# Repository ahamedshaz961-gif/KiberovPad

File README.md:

# KiberovPad

KiberovPad is a 3x3 macropad with an EC11 rotary encoder, a 128x32 OLED display, and 9 WS2812B RGB LEDs. It uses an RP2040 and QMK firmware.

I wanted to make a small macropad that I could actually use for shortcuts while also learning more about PCB design, QMK and hardware.

## Features
Custom volume control using the rotary encoder
Custom OLED animation
9 individually addressable RGB LEDs
Programmable keys using QMK
Keyboard shortcuts and macros
Compact 3x3 layout
Custom-designed PCB and case
CAD Model

The case was designed specifically for the KiberovPad PCB.

The goal was to keep it compact while still leaving enough space for the OLED, rotary encoder and RGB LEDs.

Made in Fusion 360.

## Schematic

## PCB
The PCB was designed in KiCad.

The PCB contains the 3x3 switch matrix, RP2040, rotary encoder, OLED connection and RGB LED chain.

## body

## Pinout
Function	GPIO
Row 1	GP2
Row 2	GP3
Row 3	GP4
Column 1	GP5
Column 2	GP8
Column 3	GP9
Encoder A	GP21
Encoder B	GP20
RGB Data	GP10
OLED SDA	GP6
OLED SCL	GP7

## Firmware

KiberovPad uses QMK firmware.

The current keymap includes shortcuts for things like switching tabs, copying, pasting, cutting and moving between workspaces.

The rotary encoder controls system volume.

The OLED runs a custom animation that loops continuously.

The firmware successfully compiles with QMK.

The physical hardware has not been tested yet because the parts have not arrived.

OLED

The OLED uses a custom frame animation.

RGB

The KiberovPad has 9 WS2812B RGB LEDs connected in a chain.

The RGB data line is connected to GP10.

## BOM

Here is the hardware needed to build the KiberovPad:

1x RP2040
9x MX-style mechanical switches
9x keycaps
9x 1N4148 diodes
9x WS2812B LEDs
1x EC11 rotary encoder
1x 128x32 OLED display
1x Custom KiberovPad PCB
1x Custom case
USB-C connector
Required resistors and capacitors
M3 screws / hardware for the case

## Extra Stuff

This started as a project to make my own macropad while learning more about PCB design, QMK and hardware.

It's also my first time properly working with QMK, so I added comments to the firmware because I don't know C super well yet and wanted to be able to understand and change the keymap later.

More stuff will probably be added once the hardware arrives and I can actually test it :3

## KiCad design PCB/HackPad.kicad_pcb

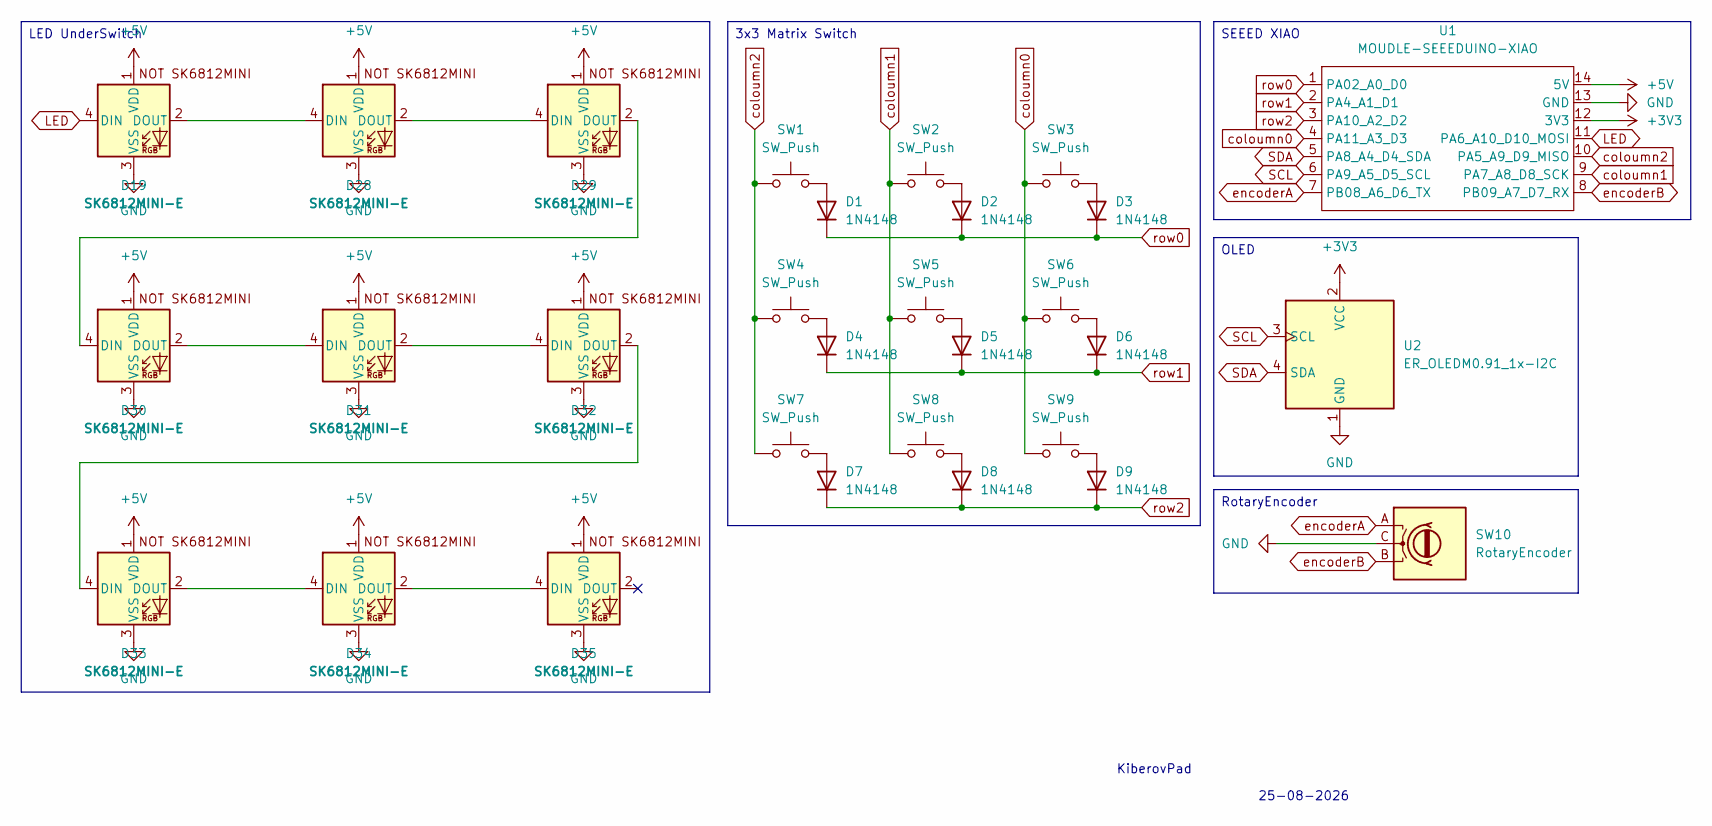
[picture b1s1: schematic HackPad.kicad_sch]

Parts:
D1, D2, D3, D4, D5, D6, D7, D8, D9: 1N4148; D_DO-35_SOD27_P7.62mm_Horizontal
D19, D28, D29, D30, D31, D32, D33, D34, D35: SK6812MINI-E; SK6812MINI-E_fixed
SW1, SW2, SW3, SW4, SW5, SW6, SW7, SW8, SW9: SW_Push; SW_Cherry_MX_1.00u_PCB
SW10: RotaryEncoder; RotaryEncoder_Alps_EC11E-Switch_Vertical_H20mm
U1: MOUDLE-SEEEDUINO-XIAO; XIAO-Generic-Hybrid-14P-2.54-21X17.8MM
U2: ER_OLEDM0.91_1x-I2C; SSD1306-0.91-OLED-4pin-128x32

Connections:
+3V3: U1.12 (3V3), U2.2 (VCC)
+5V: D19.1 (VDD), D28.1 (VDD), D29.1 (VDD), D30.1 (VDD), D31.1 (VDD), D32.1 (VDD), D33.1 (VDD), D34.1 (VDD), D35.1 (VDD), U1.14 (5V)
GND: D19.3 (VSS), D28.3 (VSS), D29.3 (VSS), D30.3 (VSS), D31.3 (VSS), D32.3 (VSS), D33.3 (VSS), D34.3 (VSS), D35.3 (VSS), SW10.C, U1.13 (GND), U2.1 (GND)
LED: D19.4 (DIN), U1.11 (PA6_A10_D10_MOSI)
unnamed: D1.2 (A), SW1.2
unnamed: D2.2 (A), SW2.2
unnamed: D3.2 (A), SW3.2
unnamed: D4.2 (A), SW4.2
unnamed: D5.2 (A), SW5.2
unnamed: D6.2 (A), SW6.2
unnamed: D7.2 (A), SW7.2
unnamed: D8.2 (A), SW8.2
unnamed: D9.2 (A), SW9.2
unnamed: D19.2 (DOUT), D28.4 (DIN)
unnamed: D28.2 (DOUT), D29.4 (DIN)
unnamed: D29.2 (DOUT), D30.4 (DIN)
unnamed: D30.2 (DOUT), D31.4 (DIN)
unnamed: D31.2 (DOUT), D32.4 (DIN)
unnamed: D32.2 (DOUT), D33.4 (DIN)
unnamed: D33.2 (DOUT), D34.4 (DIN)
unnamed: D34.2 (DOUT), D35.4 (DIN)
SCL: U1.6 (PA9_A5_D5_SCL), U2.3 (SCL)
SDA: U1.5 (PA8_A4_D4_SDA), U2.4 (SDA)
coloumn0: SW3.1, SW6.1, SW9.1, U1.4 (PA11_A3_D3)
coloumn1: SW2.1, SW5.1, SW8.1, U1.9 (PA7_A8_D8_SCK)
coloumn2: SW1.1, SW4.1, SW7.1, U1.10 (PA5_A9_D9_MISO)
encoderA: SW10.A, U1.7 (PB08_A6_D6_TX)
encoderB: SW10.B, U1.8 (PB09_A7_D7_RX)
row0: D1.1 (K), D2.1 (K), D3.1 (K), U1.1 (PA02_A0_D0)
row1: D4.1 (K), D5.1 (K), D6.1 (K), U1.2 (PA4_A1_D1)
row2: D7.1 (K), D8.1 (K), D9.1 (K), U1.3 (PA10_A2_D2)

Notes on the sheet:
25-08-2026
KiberovPad
3x3 Matrix Switch
RotaryEncoder
LED UnderSwitch
SEEED XIAO
OLED

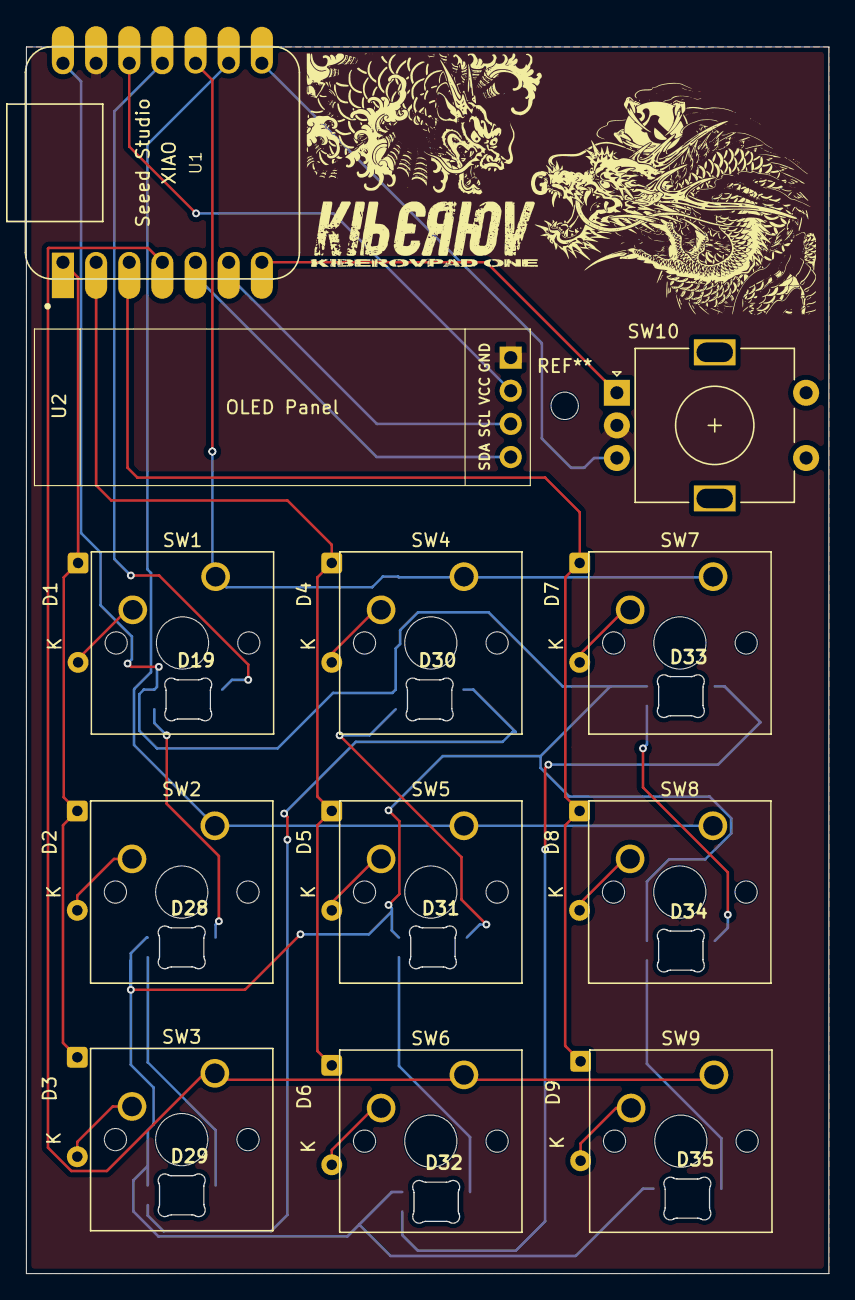
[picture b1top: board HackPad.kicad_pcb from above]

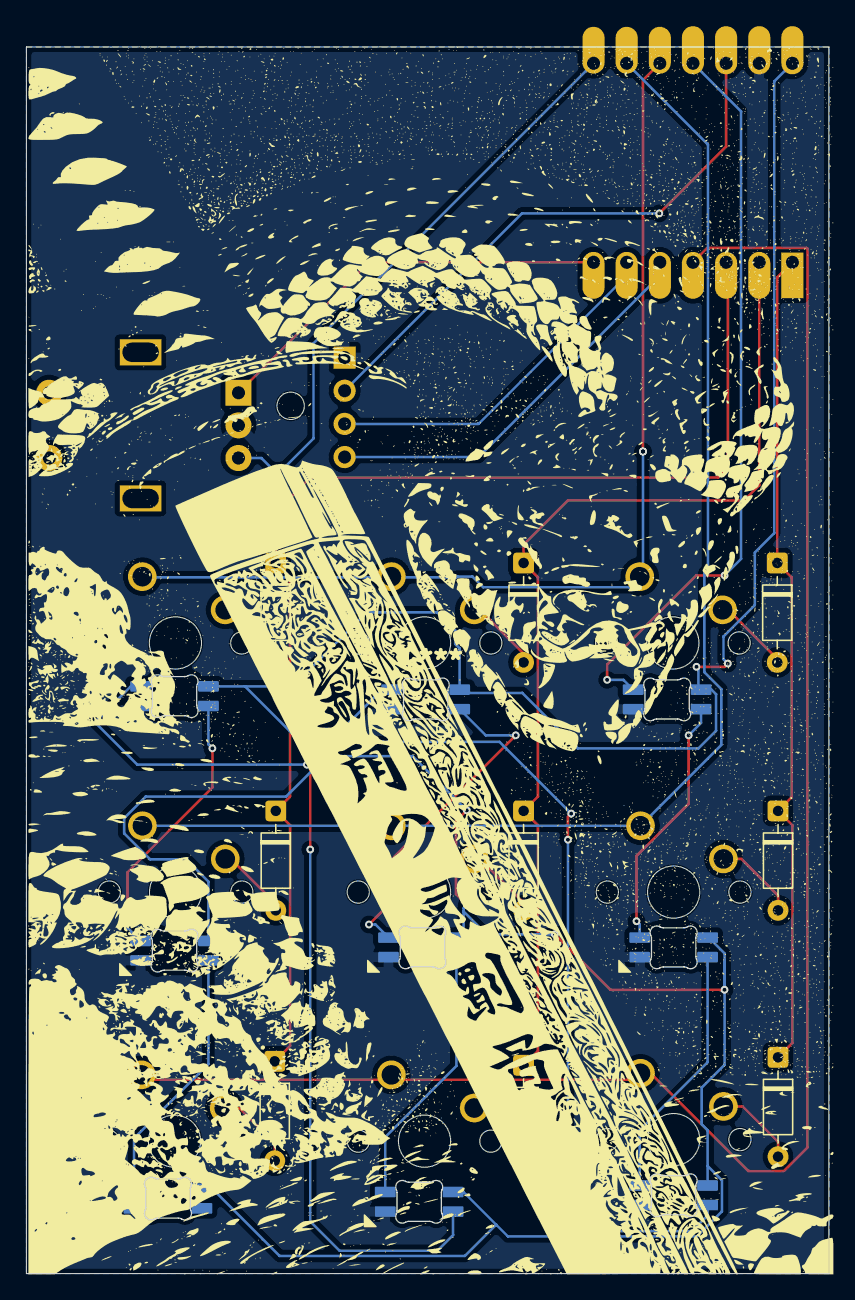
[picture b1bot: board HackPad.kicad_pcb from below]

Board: 2 copper layers, 61.5 x 94.0 mm, 30 parts (9 on the bottom side), 31 nets.
